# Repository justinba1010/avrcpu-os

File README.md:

# [Post](https://justinabaum.com/posts/2024/February/2024-02-18-Lessons-Learned-SBC)

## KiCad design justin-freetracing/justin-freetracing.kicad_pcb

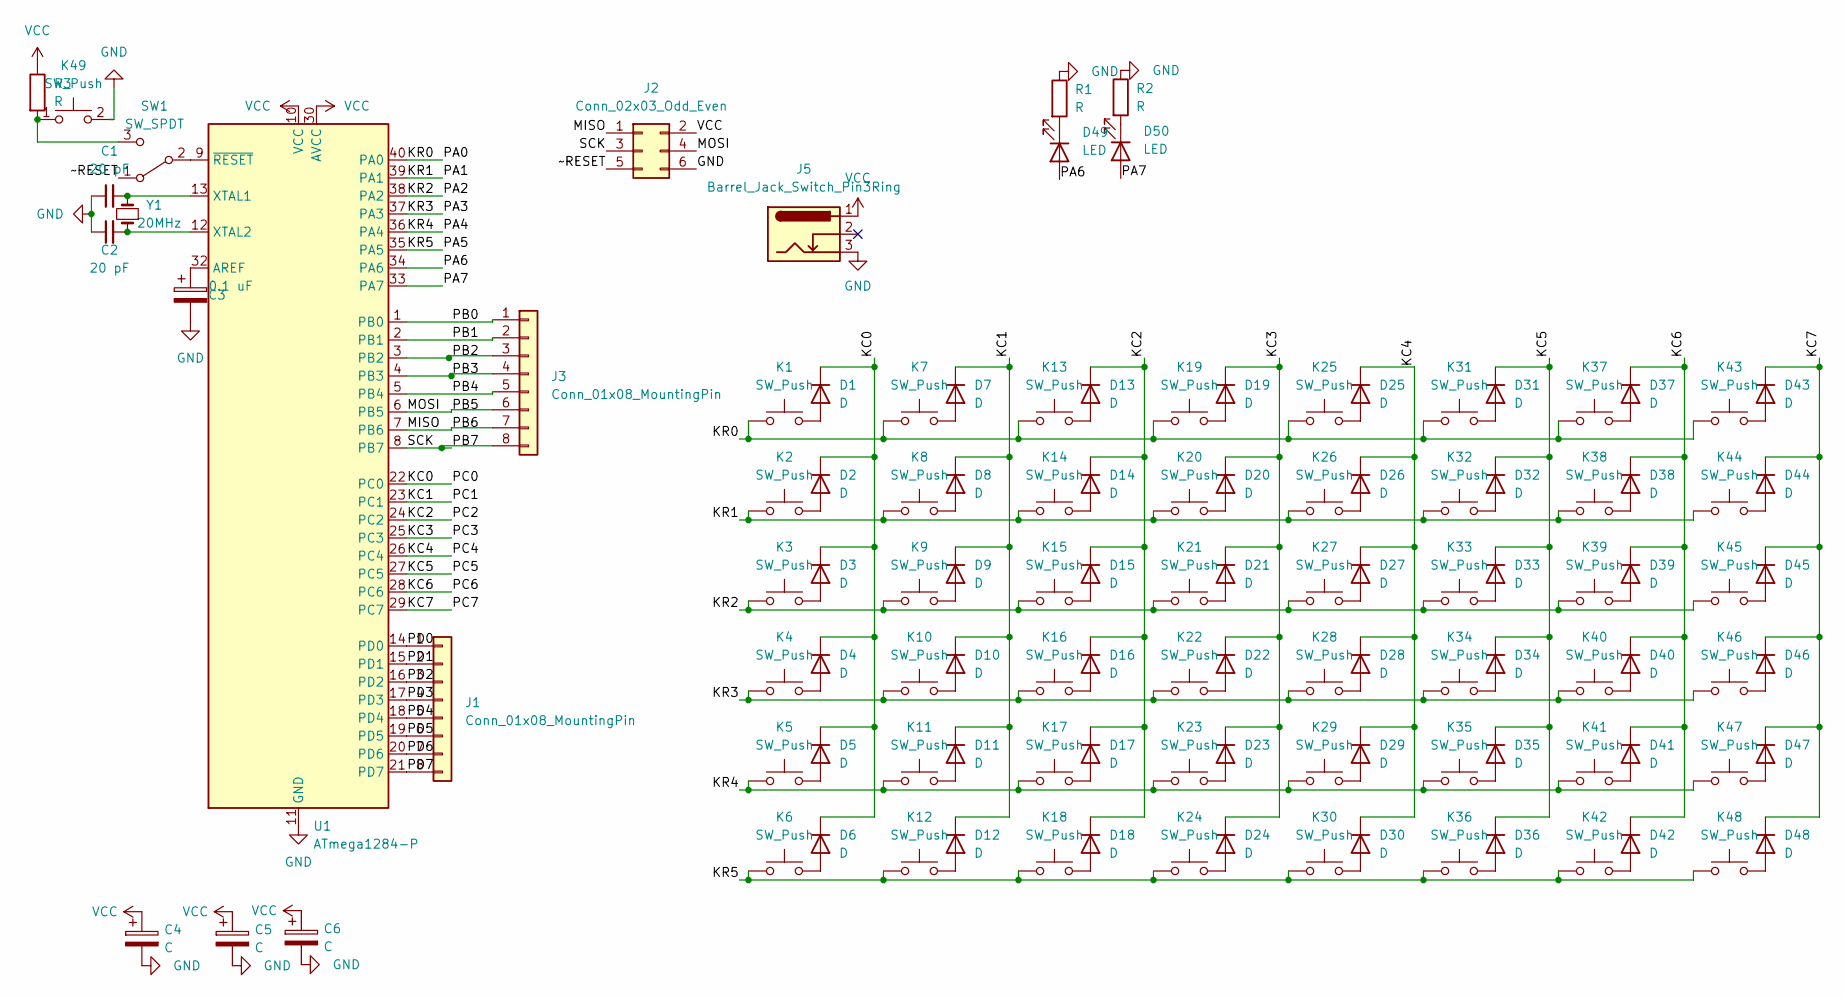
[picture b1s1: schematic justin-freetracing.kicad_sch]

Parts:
C1, C2: 20 pF; C_Disc_D3.0mm_W1.6mm_P2.50mm
C3: 0.1 uF; CP_Radial_D5.0mm_P2.00mm
C4, C5, C6: C; CP_Radial_D5.0mm_P2.00mm
D1, D2, D3, D4, D5, D6, D7, D8, D9, D10, D11, D12, D13, D14, D15, D16, D17, D18, D19, D20, D21, D22, D23, D24, D25, D26, D27, D28, D29, D30, D31, D32, D33, D34, D35, D36, D37, D38, D39, D40, D41, D42, D43, D44, D45, D46, D47, D48: D; D_DO-41_SOD81_P7.62mm_Horizontal
D49, D50: LED; LED_D5.0mm_Clear
J1, J3: Conn_01x08_MountingPin; PinHeader_1x08_P2.54mm_Vertical
J2: Conn_02x03_Odd_Even; PinHeader_2x03_P2.54mm_Vertical
J5: Barrel_Jack_Switch_Pin3Ring; BarrelJack_Horizontal
K1, K2, K3, K4, K5, K6, K7, K8, K9, K10, K11, K12, K13, K14, K15, K16, K17, K18, K19, K20, K21, K22, K23, K24, K25, K26, K27, K28, K29, K30, K31, K32, K33, K34, K35, K36, K37, K38, K39, K40, K41, K42, K43, K44, K45, K46, K47, K48, K49: SW_Push; SW_Cherry_MX_1.00u_PCB
R1, R2, R3: R; R_Axial_DIN0204_L3.6mm_D1.6mm_P7.62mm_Horizontal
SW1: SW_SPDT; PinSocket_1x03_P2.54mm_Vertical
U1: ATmega1284-P; DIP-40_W15.24mm_Socket
Y1: 20MHz; Crystal_HC49-U_Vertical

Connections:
/KC0: D1.1 (K), D2.1 (K), D3.1 (K), D4.1 (K), D5.1 (K), D6.1 (K), U1.22 (PC0)
/KC1: D7.1 (K), D8.1 (K), D9.1 (K), D10.1 (K), D11.1 (K), D12.1 (K), U1.23 (PC1)
/KC2: D13.1 (K), D14.1 (K), D15.1 (K), D16.1 (K), D17.1 (K), D18.1 (K), U1.24 (PC2)
/KC3: D19.1 (K), D20.1 (K), D21.1 (K), D22.1 (K), D23.1 (K), D24.1 (K), U1.25 (PC3)
/KC4: D25.1 (K), D26.1 (K), D27.1 (K), D28.1 (K), D29.1 (K), D30.1 (K), U1.26 (PC4)
/KC5: D31.1 (K), D32.1 (K), D33.1 (K), D34.1 (K), D35.1 (K), D36.1 (K), U1.27 (PC5)
/KC6: D37.1 (K), D38.1 (K), D39.1 (K), D40.1 (K), D41.1 (K), D42.1 (K), U1.28 (PC6)
/KC7: D43.1 (K), D44.1 (K), D45.1 (K), D46.1 (K), D47.1 (K), D48.1 (K), U1.29 (PC7)
/KR0: K1.1, K7.1, K13.1, K19.1, K25.1, K31.1, K37.1, K43.1, U1.40 (PA0)
/KR1: K2.1, K8.1, K14.1, K20.1, K26.1, K32.1, K38.1, K44.1, U1.39 (PA1)
/KR2: K3.1, K9.1, K15.1, K21.1, K27.1, K33.1, K39.1, K45.1, U1.38 (PA2)
/KR3: K4.1, K10.1, K16.1, K22.1, K28.1, K34.1, K40.1, K46.1, U1.37 (PA3)
/KR4: K5.1, K11.1, K17.1, K23.1, K29.1, K35.1, K41.1, K47.1, U1.36 (PA4)
/KR5: K6.1, K12.1, K18.1, K24.1, K30.1, K36.1, K42.1, K48.1, U1.35 (PA5)
/MISO: J2.1, J3.7, U1.7 (PB6)
/MOSI: J2.4, J3.6, U1.6 (PB5)
/PA6: D49.2 (A), U1.34 (PA6)
/PA7: D50.2 (A), U1.33 (PA7)
/PB0: J3.1, U1.1 (PB0)
/PB1: J3.2, U1.2 (PB1)
/PB2: J3.3, U1.3 (PB2)
/PB3: J3.4, U1.4 (PB3)
/PB4: J3.5, U1.5 (PB4)
/PB7: J2.3, J3.8, U1.8 (PB7)
/PD0: J1.1, U1.14 (PD0)
/PD1: J1.2, U1.15 (PD1)
/PD2: J1.3, U1.16 (PD2)
/PD3: J1.4, U1.17 (PD3)
/PD4: J1.5, U1.18 (PD4)
/PD5: J1.6, U1.19 (PD5)
/PD6: J1.7, U1.20 (PD6)
/PD7: J1.8, U1.21 (PD7)
/~RESET: J2.5, SW1.1 (A)
GND: C1.1, C2.1, C3.2, C4.2, C5.2, C6.2, J2.6, J5.3, K49.2, R1.1, R2.1, U1.11 (GND), U1.31 (GND)
unnamed: C1.2, U1.13 (XTAL1), Y1.2
unnamed: C2.2, U1.12 (XTAL2), Y1.1
unnamed: C3.1, U1.32 (AREF)
unnamed: D1.2 (A), K1.2
unnamed: D2.2 (A), K2.2
unnamed: D3.2 (A), K3.2
unnamed: D4.2 (A), K4.2
unnamed: D5.2 (A), K5.2
unnamed: D6.2 (A), K6.2
unnamed: D7.2 (A), K7.2
unnamed: D8.2 (A), K8.2
unnamed: D9.2 (A), K9.2
unnamed: D10.2 (A), K10.2
unnamed: D11.2 (A), K11.2
unnamed: D12.2 (A), K12.2
unnamed: D13.2 (A), K13.2
unnamed: D14.2 (A), K14.2
unnamed: D15.2 (A), K15.2
unnamed: D16.2 (A), K16.2
unnamed: D17.2 (A), K17.2
unnamed: D18.2 (A), K18.2
unnamed: D19.2 (A), K19.2
unnamed: D20.2 (A), K20.2
unnamed: D21.2 (A), K21.2
unnamed: D22.2 (A), K22.2
unnamed: D23.2 (A), K23.2
unnamed: D24.2 (A), K24.2
unnamed: D25.2 (A), K25.2
unnamed: D26.2 (A), K26.2
unnamed: D27.2 (A), K27.2
unnamed: D28.2 (A), K28.2
unnamed: D29.2 (A), K29.2
unnamed: D30.2 (A), K30.2
unnamed: D31.2 (A), K31.2
unnamed: D32.2 (A), K32.2
unnamed: D33.2 (A), K33.2
unnamed: D34.2 (A), K34.2
unnamed: D35.2 (A), K35.2
unnamed: D36.2 (A), K36.2
unnamed: D37.2 (A), K37.2
unnamed: D38.2 (A), K38.2
unnamed: D39.2 (A), K39.2
unnamed: D40.2 (A), K40.2
unnamed: D41.2 (A), K41.2
unnamed: D42.2 (A), K42.2
unnamed: D43.2 (A), K43.2
unnamed: D44.2 (A), K44.2
unnamed: D45.2 (A), K45.2
unnamed: D46.2 (A), K46.2
unnamed: D47.2 (A), K47.2
unnamed: D48.2 (A), K48.2
unnamed: D49.1 (K), R1.2
unnamed: D50.1 (K), R2.2
unnamed: K49.1, R3.2, SW1.3 (C)
unnamed: SW1.2 (B), U1.9 (~RESET)
VCC: C4.1, C5.1, C6.1, J2.2, J5.1, R3.1, U1.10 (VCC), U1.30 (AVCC)

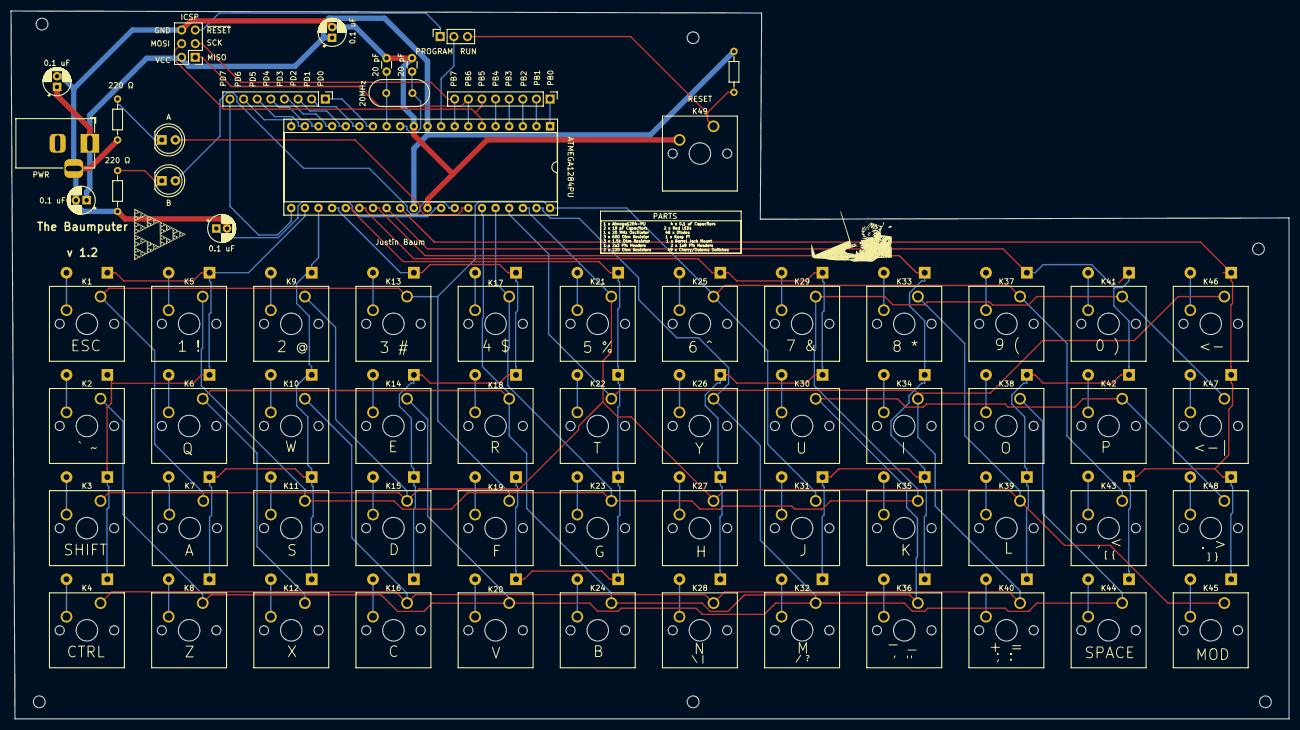
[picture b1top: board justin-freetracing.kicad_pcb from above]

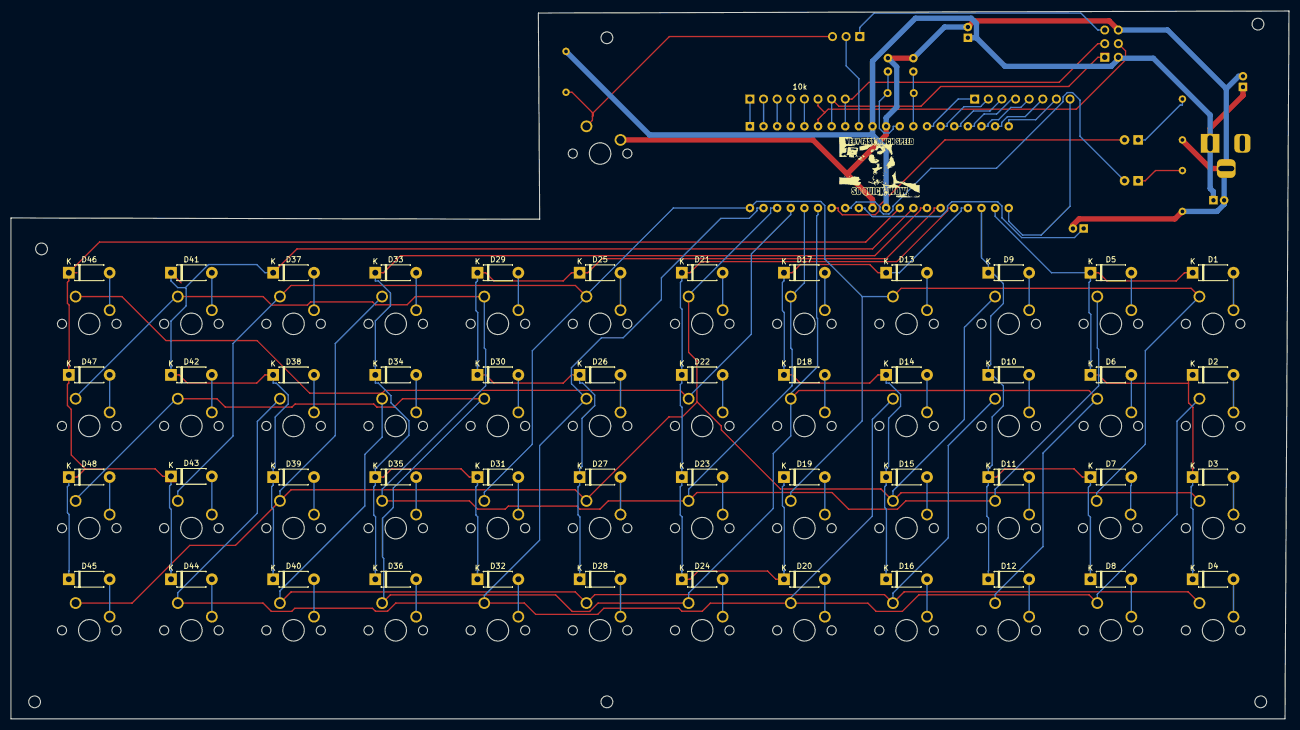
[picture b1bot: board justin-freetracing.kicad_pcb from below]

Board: 2 copper layers, 238.3 x 132.0 mm, 124 parts (49 on the bottom side), 90 nets.

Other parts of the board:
G1: LOGO; cat computer
G2: LOGO; sierpinski
G3: LOGO; fast
REF1, REF2, REF3, REF4, REF6, REF7: MountingHole_2.2mm_M2

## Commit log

2022-08-08 Additional
2022-08-21 AVR Update
    Clang Tidy
2022-09-02 Testing LEDs Live
2023-09-12 Push
